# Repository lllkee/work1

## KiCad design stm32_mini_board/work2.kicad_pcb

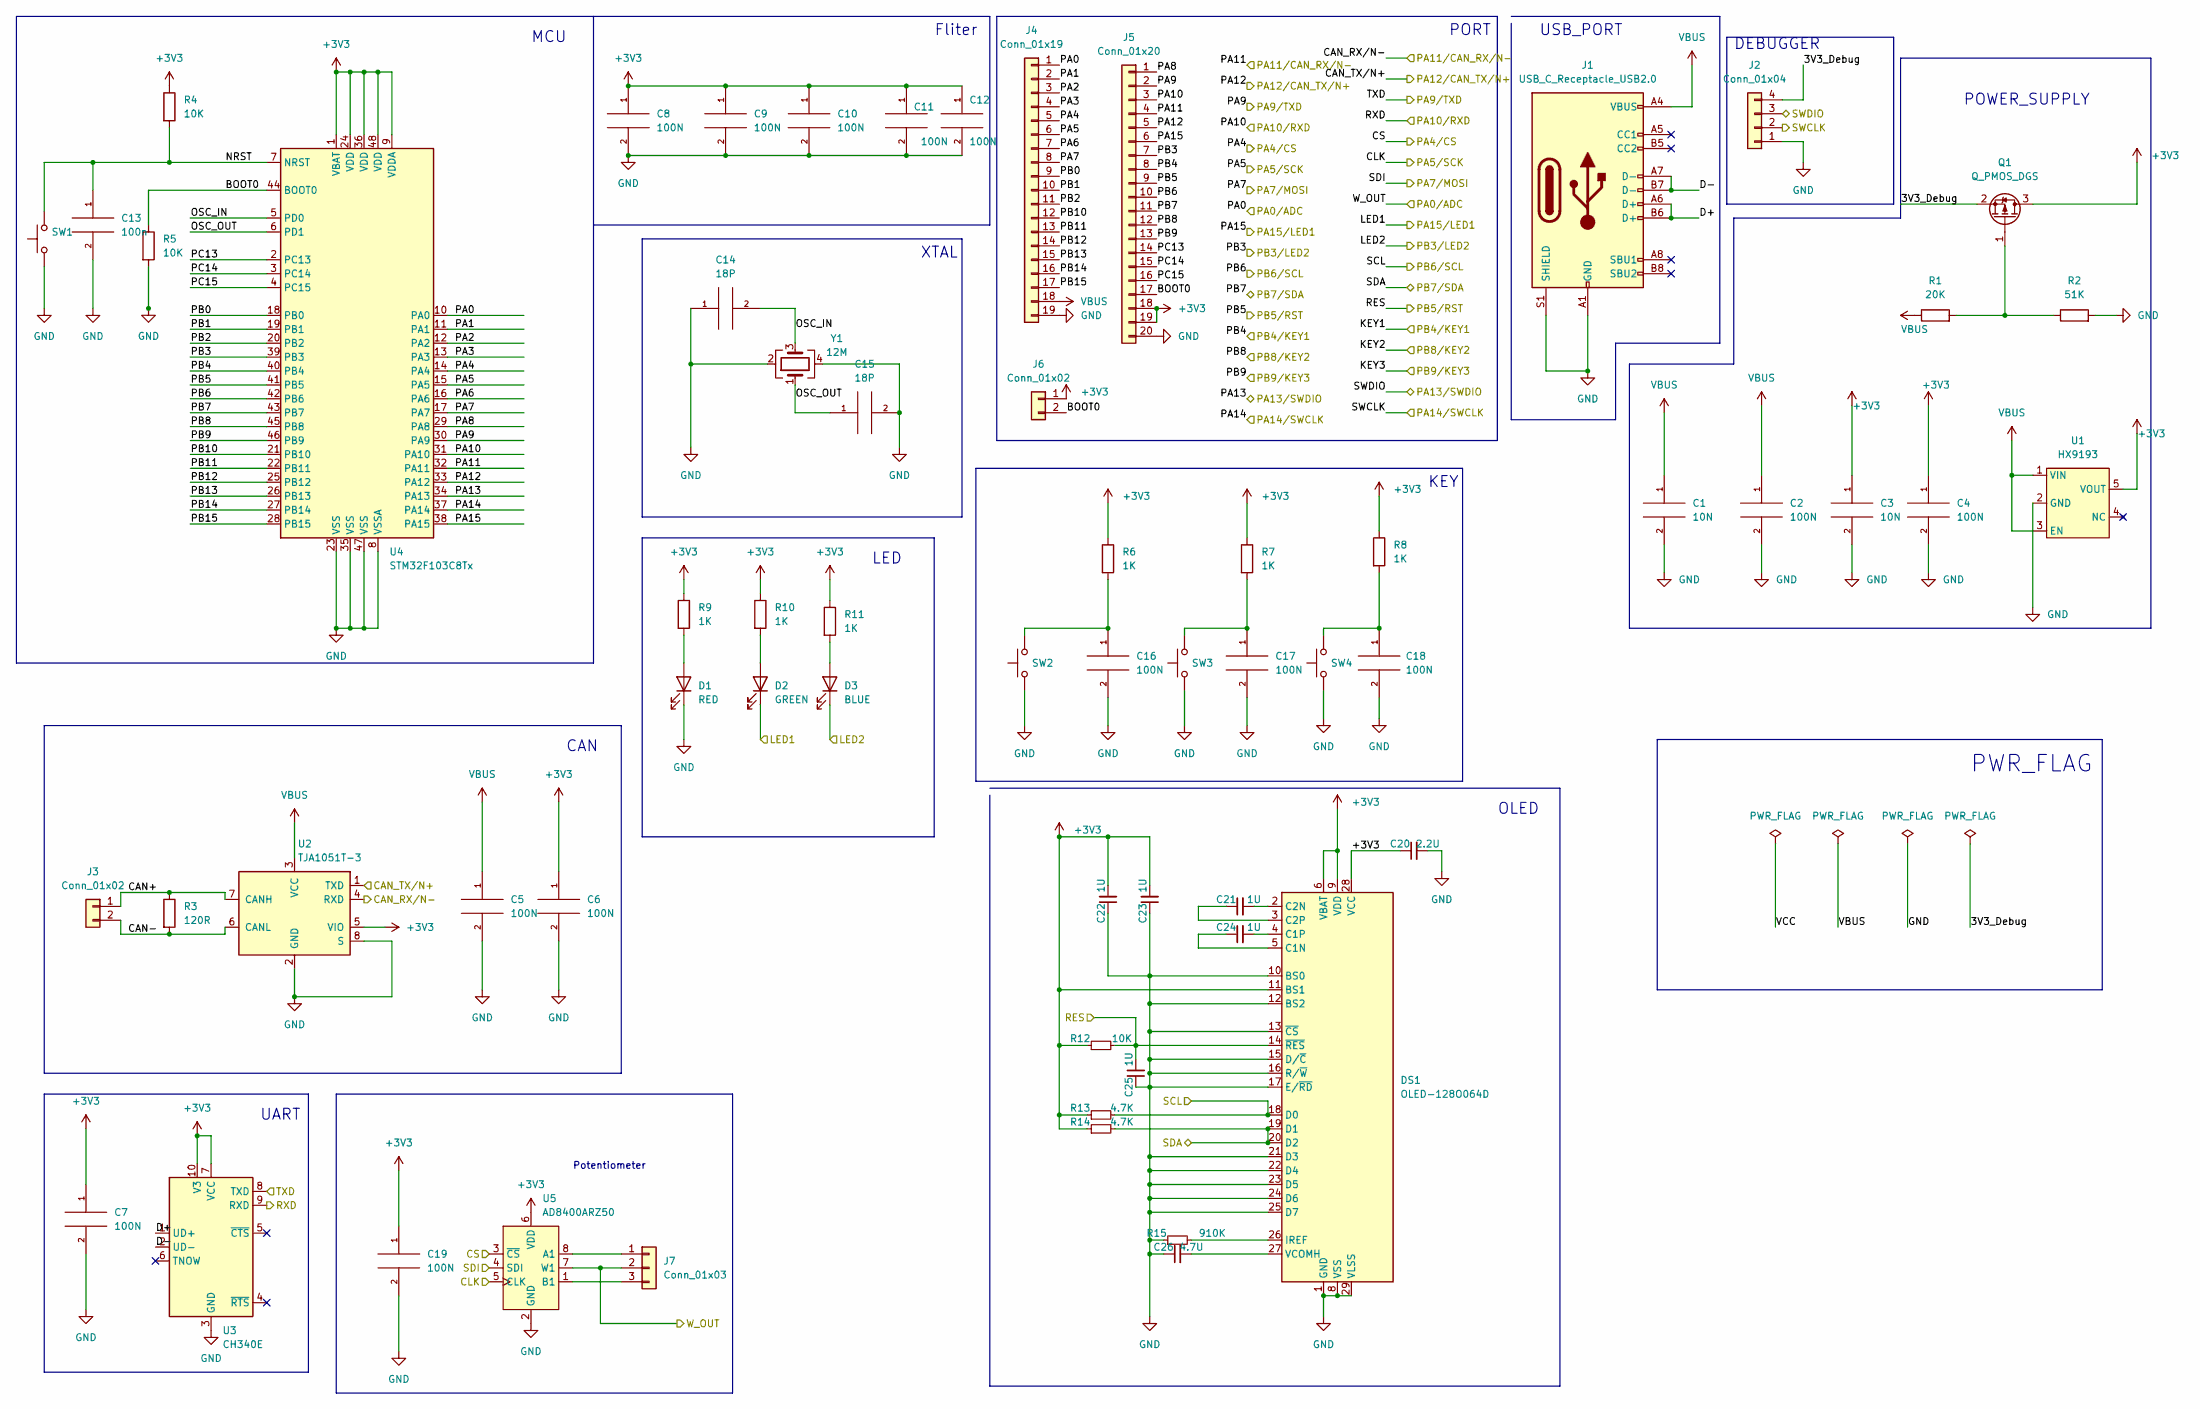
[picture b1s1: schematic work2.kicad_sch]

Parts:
C1, C3: 10N; C_0603_1608Metric
C2, C4, C5, C6, C7, C8, C9, C10, C11, C12, C16, C17, C18, C19: 100N; C_0603_1608Metric
C13: 100n; C_0603_1608Metric
C14, C15: 18P; C_0603_1608Metric
C20: 2.2U; C_0603_1608Metric
C21, C22, C23, C24, C25: 1U; C_0603_1608Metric
C26: 4.7U; C_0603_1608Metric
D1: RED; LED_0603_1608Metric
D2: GREEN; LED_0603_1608Metric
D3: BLUE; LED_0603_1608Metric
DS1: OLED-128O064D
J1: USB_C_Receptacle_USB2.0; USB_C_Receptacle_Palconn_UTC16-G
J2: Conn_01x04; PinHeader_1x04_P2.54mm_Vertical
J3: Conn_01x02; JST_GH_SM02B-GHS-TB_1x02-1MP_P1.25mm_Horizontal
J4: Conn_01x19; PinHeader_1x19_P2.54mm_Vertical
J5: Conn_01x20; PinHeader_1x20_P2.54mm_Vertical
J6: Conn_01x02; PinHeader_1x02_P2.54mm_Vertical
J7: Conn_01x03; PinHeader_1x03_P2.54mm_Vertical
Q1: Q_PMOS_DGS; TSOT-23
R1: 20K; R_0603_1608Metric
R2: 51K; R_0603_1608Metric
R3: 120R; R_0603_1608Metric
R4, R5, R12: 10K; R_0603_1608Metric
R6, R7, R8, R9, R10, R11: 1K; R_0603_1608Metric
R13, R14: 4.7K; R_0603_1608Metric
R15: 910K; R_0603_1608Metric
SW1, SW2, SW3, SW4: SW_Push; SW_Push_1P1T_NO_6x6mm_H9.5mm
U1: HX9193; SOT-23-5_HandSoldering
U2: TJA1051T-3; SOIC-8_3.9x4.9mm_P1.27mm
U3: CH340E; MSOP-10_3x3mm_P0.5mm
U4: STM32F103C8Tx; LQFP-48_7x7mm_P0.5mm
U5: AD8400ARZ50; SOP-8_3.9x4.9mm_P1.27mm
Y1: 12M; Crystal_SMD_3225-4Pin_3.2x2.5mm

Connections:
+3V3: C3.1, C4.1, C6.1, C7.1, C8.1, C9.1, C10.1, C11.1, C12.1, C19.1, C20.1, C22.2, C23.2, DS1.6 (VBAT), DS1.9 (VDD), DS1.11 (BS1), DS1.28 (VCC), J5.18, J5.19, J6.1, Q1.3 (D), R4.1, R6.1, R7.1, R8.1, R9.1, R10.1, R11.1, R12.1, R13.1, R14.1, U1.5 (VOUT), U2.5 (VIO), U3.7 (VCC), U3.10 (V3), U4.1 (VBAT), U4.9 (VDDA), U4.24 (VDD), U4.36 (VDD), U4.48 (VDD), U5.6 (VDD)
/3V3_Debug: J2.4, Q1.2 (S)
/BOOT0: J5.17, J6.2, R5.1, U4.44 (BOOT0)
/CAN+: J3.1, R3.1, U2.7 (CANH)
/CAN-: J3.2, R3.2, U2.6 (CANL)
/CAN_TX/N+: J5.5, U2.1 (TXD), U4.33 (PA12)
/CLK: J4.6, U4.15 (PA5), U5.5 (CLK)
/CS: J4.5, U4.14 (PA4), U5.3 (~CS)
/D+: J1.A6 (D+), J1.B6 (D+), U3.1 (UD+)
/D-: J1.A7 (D-), J1.B7 (D-), U3.2 (UD-)
/KEY1: J5.8, U4.40 (PB4)
/KEY2: J5.12, U4.45 (PB8)
/KEY3: J5.13, U4.46 (PB9)
/LED1: D2.1 (K), J5.6, U4.38 (PA15)
/LED2: D3.1 (K), J5.7, U4.39 (PB3)
/NRST: C13.1, R4.2, SW1.2, U4.7 (NRST)
/OSC_IN: C14.2, U4.5 (PD0), Y1.3
/OSC_OUT: C15.1, U4.6 (PD1), Y1.1
/PA0: J4.1, J7.2, U4.10 (PA0), U5.7 (W1)
/PA1: J4.2, U4.11 (PA1)
/PA2: J4.3, U4.12 (PA2)
/PA3: J4.4, U4.13 (PA3)
/PA6: J4.7, U4.16 (PA6)
/PA7: J4.8, U4.17 (PA7), U5.4 (SDI)
/PA8: J5.1, U4.29 (PA8)
/PA9: J5.2, U3.8 (TXD), U4.30 (PA9)
/PA10: J5.3, U3.9 (RXD), U4.31 (PA10)
/PA11: J5.4, U2.4 (RXD), U4.32 (PA11)
/PA13: J2.3, U4.34 (PA13)
/PA14: J2.2, U4.37 (PA14)
/PB0: J4.9, U4.18 (PB0)
/PB1: J4.10, U4.19 (PB1)
/PB2: J4.11, U4.20 (PB2)
/PB5: C25.2, DS1.14 (~RES), J5.9, R12.2, U4.41 (PB5)
/PB6: DS1.18 (D0), J5.10, R13.2, U4.42 (PB6)
/PB7: DS1.19 (D1), DS1.20 (D2), J5.11, R14.2, U4.43 (PB7)
/PB10: J4.12, U4.21 (PB10)
/PB11: J4.13, U4.22 (PB11)
/PB12: J4.14, U4.25 (PB12)
/PB13: J4.15, U4.26 (PB13)
/PB14: J4.16, U4.27 (PB14)
/PB15: J4.17, U4.28 (PB15)
/PC13: J5.14, U4.2 (PC13)
/PC14: J5.15, U4.3 (PC14)
/PC15: J5.16, U4.4 (PC15)
GND: C1.2, C2.2, C3.2, C4.2, C5.2, C6.2, C7.2, C8.2, C9.2, C10.2, C11.2, C12.2, C13.2, C14.1, C15.2, C16.2, C17.2, C18.2, C19.2, C20.2, C22.1, C23.1, C25.1, C26.1, D1.1 (K), DS1.1 (GND), DS1.8 (VSS), DS1.10 (BS0), DS1.12 (BS2), DS1.13 (~CS), DS1.15 (D/~C), DS1.16 (R/~W), DS1.17 (E/~RD), DS1.21 (D3), DS1.22 (D4), DS1.23 (D5), DS1.24 (D6), DS1.25 (D7), DS1.29 (VLSS), DS1.30 (GND), J1.A1 (GND), J1.A12 (GND), J1.B1 (GND), J1.B12 (GND), J1.S1 (SHIELD), J2.1, J4.19, J5.20, R2.2, R5.2, R15.1, SW1.1, SW2.1, SW3.1, SW4.1, U1.2 (GND), U2.2 (GND), U2.8 (S), U3.3 (GND), U4.8 (VSSA), U4.23 (VSS), U4.35 (VSS), U4.47 (VSS), U5.2 (GND), Y1.2, Y1.4
unnamed: C16.1, R6.2, SW2.2
unnamed: C17.1, R7.2, SW3.2
unnamed: C18.1, R8.2, SW4.2
unnamed: C21.1, DS1.3 (C2P)
unnamed: C21.2, DS1.2 (C2N)
unnamed: C24.1, DS1.5 (C1N)
unnamed: C24.2, DS1.4 (C1P)
unnamed: C26.2, DS1.27 (VCOMH)
unnamed: D1.2 (A), R9.2
unnamed: D2.2 (A), R10.2
unnamed: D3.2 (A), R11.2
unnamed: DS1.26 (IREF), R15.2
unnamed: J7.1, U5.8 (A1)
unnamed: J7.3, U5.1 (B1)
unnamed: Q1.1 (G), R1.2, R2.1
VBUS: C1.1, C2.1, C5.1, J1.A4 (VBUS), J1.A9 (VBUS), J1.B4 (VBUS), J1.B9 (VBUS), J4.18, R1.1, U1.1 (VIN), U1.3 (EN), U2.3 (VCC)

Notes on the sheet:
Fliter
MCU
KEY
CAN
PORT
XTAL
USB_PORT
DEBUGGER
Potentiometer
LED
OLED
UART
POWER_SUPPLY
PWR_FLAG

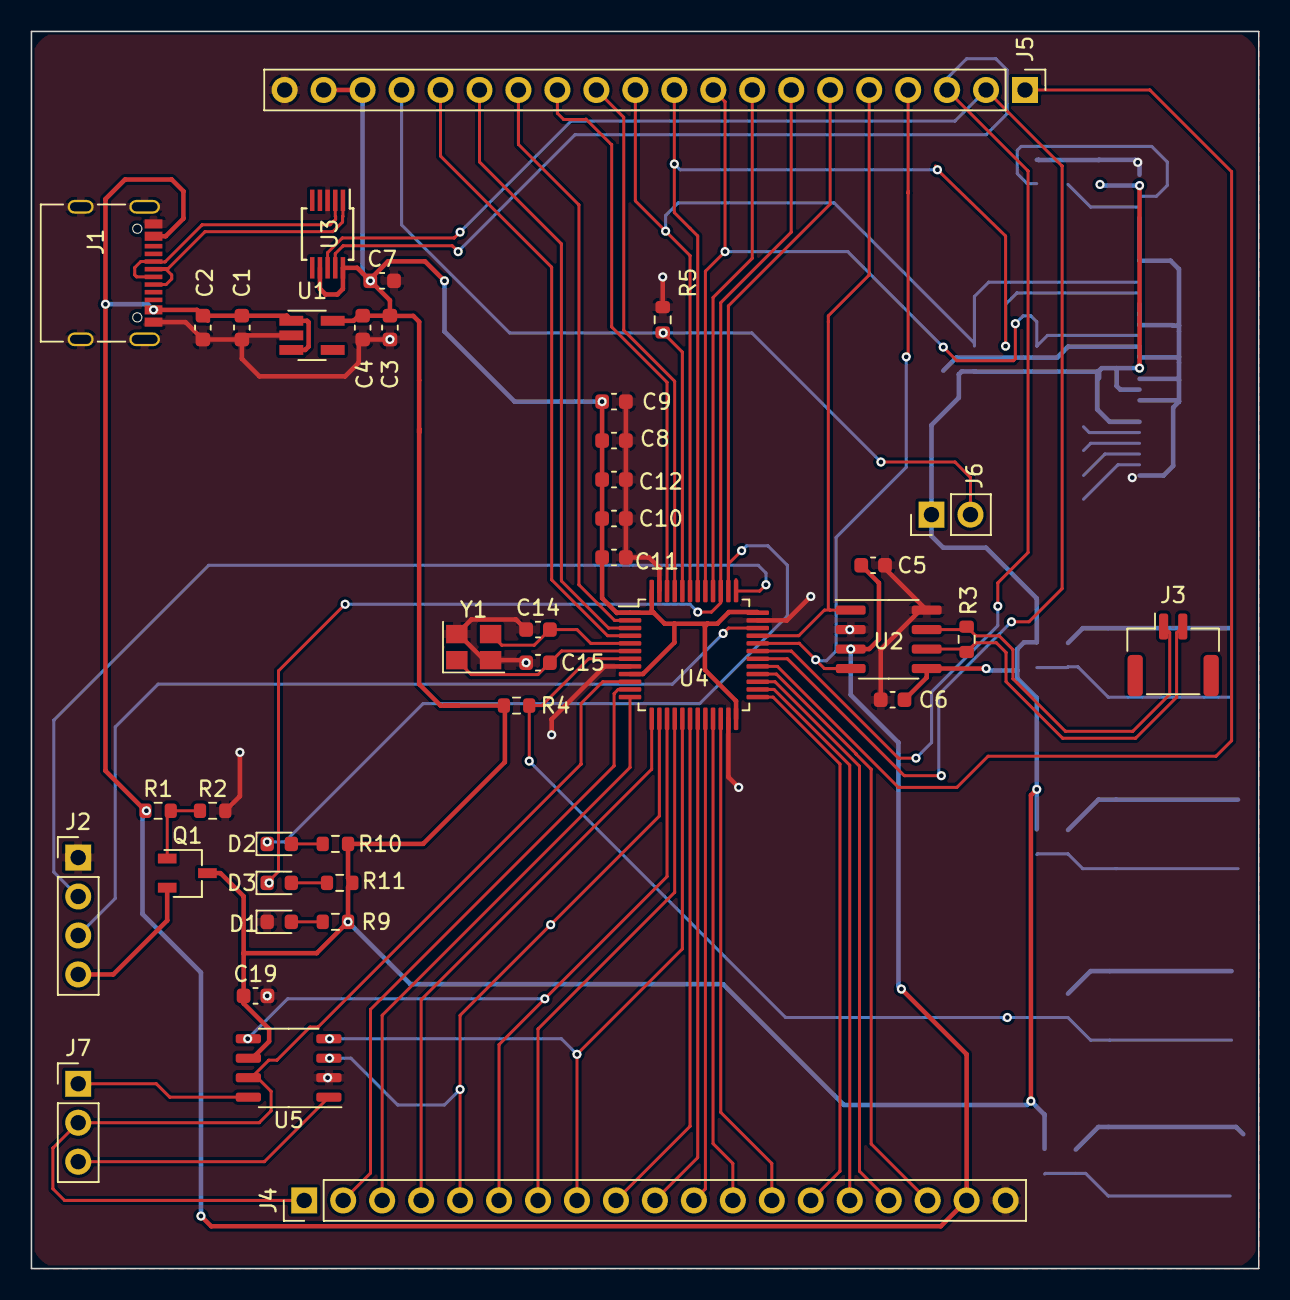
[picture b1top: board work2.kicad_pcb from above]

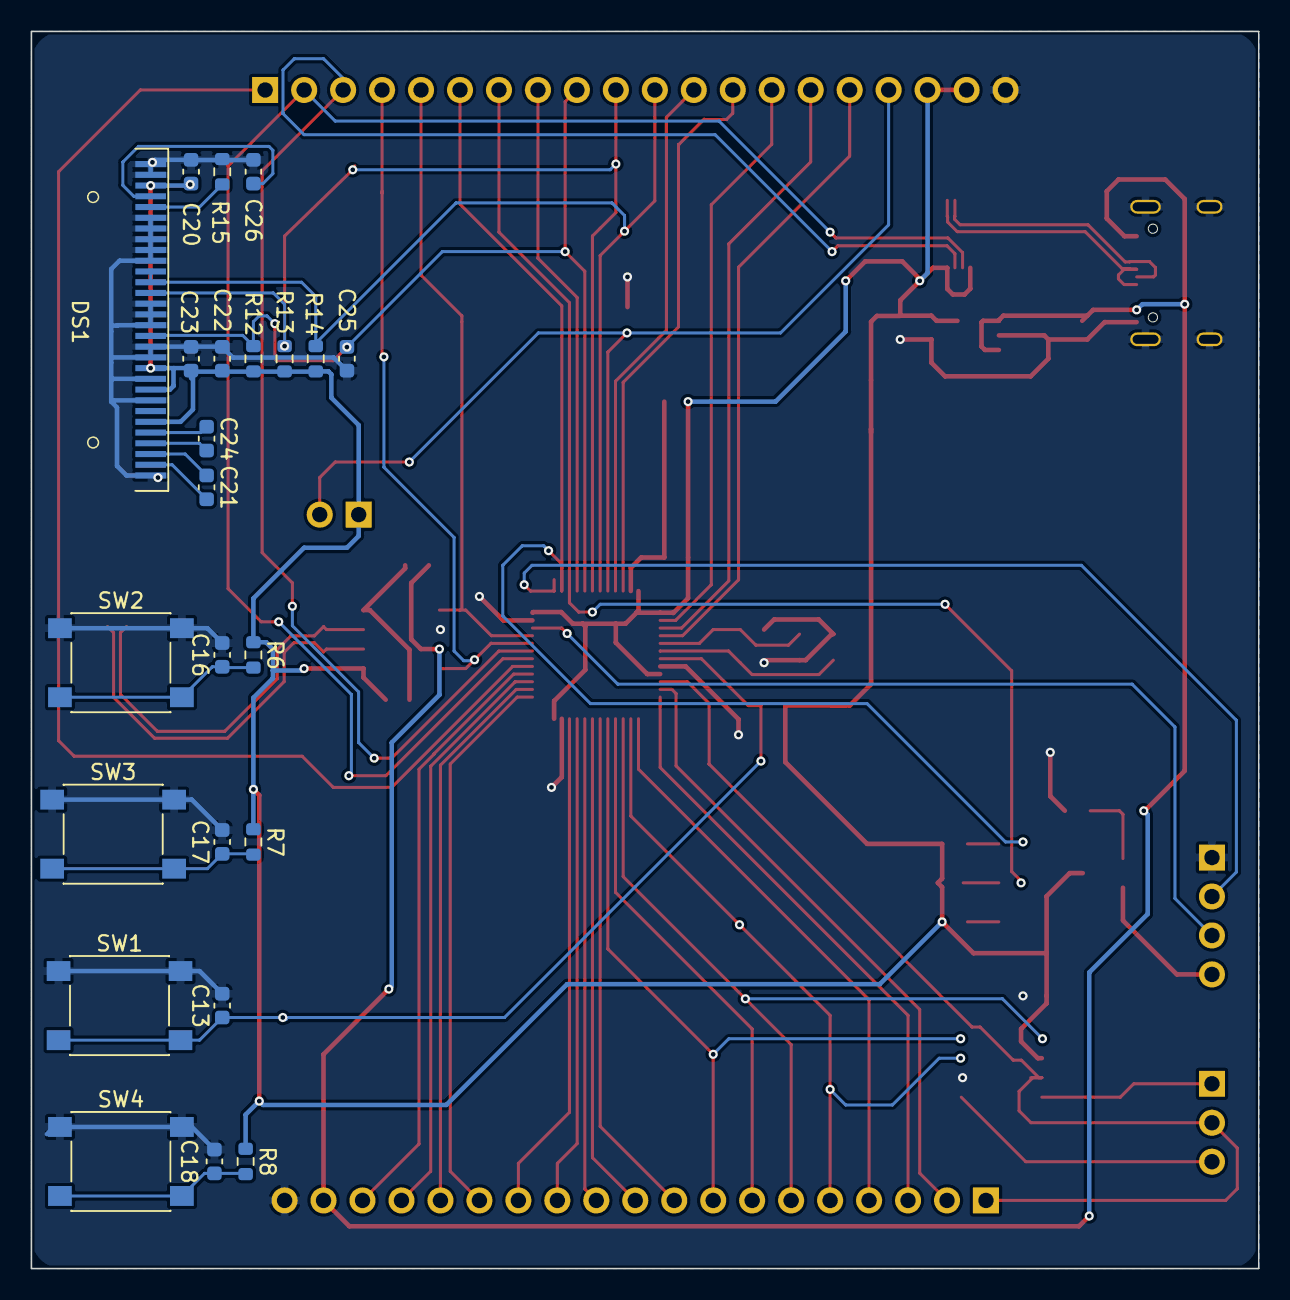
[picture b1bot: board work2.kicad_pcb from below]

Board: 2 copper layers, 80.0 x 80.6 mm, 63 parts (23 on the bottom side), 62 nets.

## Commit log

2022-10-04 Add 123.txt
2022-10-06 stm32_board
